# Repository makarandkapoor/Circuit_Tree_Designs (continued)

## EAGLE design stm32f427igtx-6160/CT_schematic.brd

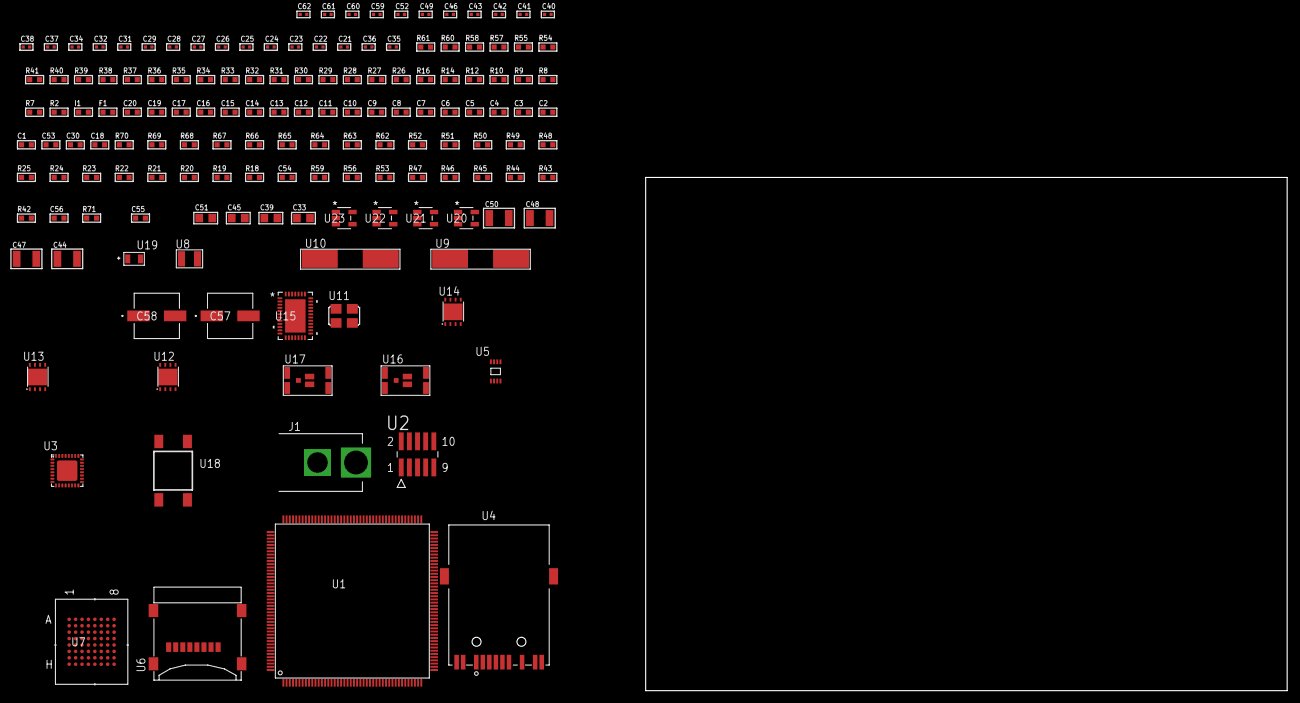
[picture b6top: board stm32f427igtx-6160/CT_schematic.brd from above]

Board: 2 copper layers, 100.0 x 80.0 mm, 150 parts (0 on the bottom side), 137 nets, no tracks yet.

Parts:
C1, C20: 1e-06; C0603
C2, C3, C4, C5, C6, C7, C8, C9, C10, C11, C12, C13, C14, C15, C16, C17: 1e-07; C0603
C18: 4.7e-06; C0603
C19: 1e-08; C0603
C21, C22, C27, C28, C29, C31, C32, C34, C38, C52: 1e-07; C0402
C23, C24, C25, C26: 1e-11; C0402
C30, C53: 2.2e-06; C0603
C33, C39, C45, C51: 1e-05; C0805
C35, C36: 2.2e-11; C0402
C37, C40, C41, C42, C43, C46, C49, C59, C60, C61, C62: 1e-08; C0402
C44, C47, C48, C50: 1e-05; C1210
C54: 2.45e-08; R0603
C55: 2.8258362168397e-09; R0603
C56: 7.105e-09; R0603
C57, C58: 0.0001; EXV-9H
F1: 240.0; L0603
I1: 97.0; R0603
J1: PJ-037B; PJ-037B_PACKAGE
R2, R36, R38, R39, R40, R55, R58, R61: 1000.0; R0603
R7, R8, R9, R32, R33, R34, R35, R37, R41: 4700.0; R0603
R10, R12, R14, R16: 2200.0; R0603
R18, R19, R20, R21, R22, R23, R24, R25, R48, R49, R50, R51, R52, R62, R64, R65, R68, R69, R70: 10000.0; R0603
R26: 5.0; R0603
R27, R28: 0.1; R0603
R29, R54, R60: 200.0; R0603
R30: 220.0; R0603
R31: 6490.0; R0603
R42, R43, R44, R45, R46, R47, R53, R56, R59: 100000.0; R0603
R57: 2231.0; R0603
R63: 75000.0; R0603
R66, R67: 95300.0; R0603
R71: 104236.36363636; R0603
U1: STM32F427IGT6; LQFP176
U2: FTSH-105-01-L-DV-K; SAMTEC_FTSH-105-01-L-DV-K
U3: KSZ8081RNBIA-TR; QFN-32
U4: 7498011122R
U5: 24AA02T-I/MNY; TDFN-8/6MM
U6: 0472192001; MOLEX_47219-2001
U7: mt28ew256aba1HPC-0SIT; LBGA-64
U8: ABS07-32.768KHZ-7-T
U9, U10: ABLS-25.000MHZ-B2F-T
U11: ASFL1-50MHZ-NCS; ASFL1
U12, U13, U14: LP3878SDX-ADJ/NOPB; WSON-8
U15: LTC2928CUHF#PBF; QFN-38_UHF
U16, U17: IRF8306MTRPbF; IRF8306MTRPBF
U18: 4-1437565-2; SW_4-1437565-2
U19: Q65110A2395; LGM67K-G1J2-24-Z
U20, U21, U22, U23: nc7sz125m5x; NC7SZ125M5X

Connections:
CLK_CRYSTAL_U1_9: C23.1, U1.9, U8.1
CLK_CRYSTAL_U1_10: C24.1, U1.10, U8.2
CLK_CRYSTAL_U1_29: C25.1, U1.29, U9.1
CLK_CRYSTAL_U1_30: C26.1, U1.30, U9.2
CLK_CRYSTAL_U3_8: C35.1, U3.8, U10.2
CLK_CRYSTAL_U3_9: C36.1, U3.9, U10.1
CLK_U1_41: U1.41, U11.3
GND: C1.2, C2.2, C3.2, C4.2, C5.2, C6.2, C7.2, C8.2, C9.2, C10.2, C11.2, C12.2, C13.2, C14.2, C15.2, C16.2, C17.2, C18.2, C19.2, C20.2, C21.2, C22.2, C23.2, C24.2, C25.2, C26.2, C27.2, C28.2, C29.2, C30.2, C31.2, C32.2, C33.2, C34.2, C35.2, C36.2, C37.2, C38.2, C39.2, C40.2, C41.2, C42.2, C43.2, C44.2, C45.2, C46.2, C47.2, C48.2, C49.2, C50.2, C51.2, C52.2, C53.2, C54.2, C55.2, C56.2, C57.2, C58.2, C59.2, C60.2, C61.2, C62.2, J1.2, R2.2, R20.2, R25.2, R26.2, R27.2, R28.2, R31.2, R33.2, R36.2, R38.2, R39.2, R40.2, R55.2, R58.2, R61.2, R63.2, R66.2, R67.2, R68.2, R69.2, R70.2, U1.14, U1.22, U1.37, U1.61, U1.71, U1.90, U1.102, U1.113, U1.126, U1.135, U1.148, U1.158, U2.3, U2.5, U3.1, U3.EXP, U4.1, U4.10, U5.4, U5.7, U6.6, U6.G1, U6.G2, U6.G3, U6.G4, U7.E8, U7.H2, U7.H7, U11.2, U12.3, U12.PAD, U13.3, U13.PAD, U14.3, U14.PAD, U15.8, U15.9, U15.10, U15.12, U15.13, U15.24, U15.25, U15.30, U15.32, U15.39, U19.C, U20.2, U20.3, U21.1, U21.3, U22.1, U22.3, U23.1, U23.3
NET_U1_31: R9.1, U1.31, U23.4
NET_U1_33: R14.1, U1.33, U3.12
NET_U1_39: C19.1, C20.1, F1.1, U1.38, U1.39
NET_U1_42: R16.1, U1.42, U3.11
NET_U1_48: R21.1, U1.48
NET_U1_58: R20.1, U1.58
NET_U1_125: C22.1, U1.125
NET_U1_164: R10.1, U1.164, U5.6
NET_U1_165: R12.1, U1.165, U5.5
NET_U1_166: R19.1, U1.166
NET_U1_171: R18.1, U1.171
NET_U1_176: U18.3, U18.4
NET_U2_9: R26.1, U2.9
NET_U3_2: C30.1, C31.1, U3.2
NET_U3_3: C32.1, I1.1, U3.3
NET_U3_10: R31.1, U3.10
NET_U3_13: R34.1, U3.13
NET_U3_14: R35.1, U3.14
NET_U3_19: R33.1, U3.19
NET_U3_20: R39.1, U3.20
NET_U3_21: R32.1, U3.21
NET_U3_28: R37.1, U3.28
NET_U3_29: R38.1, U3.29
NET_U3_31: R40.1, U3.31
NET_U3_32: R7.1, U3.32, U21.4
NET_U4_1: U3.7, U4.1
NET_U4_2: C28.1, U4.2
NET_U4_3: U3.6, U4.3
NET_U4_4: U3.5, U4.4
NET_U4_5: C29.1, U4.5
NET_U4_6: U3.4, U4.6
NET_U4_8: R28.1, U4.8
NET_U4_9: R29.1, U4.9
NET_U4_12: R30.1, U4.12
NET_U4_13: R27.1, U4.13, U4.14
NET_U7_B4: R51.1, U7.B4
NET_U7_B5: R8.1, U7.B5, U22.4
NET_U12_1: C43.1, U12.1
NET_U12_6: R54.2, R55.1, U12.6
NET_U12_8: R53.1, U12.8
NET_U13_1: C46.1, U13.1
NET_U13_6: R57.2, R58.1, U13.6
NET_U13_8: R56.1, U13.8
NET_U14_1: C49.1, U14.1
NET_U14_6: R60.2, R61.1, U14.6
NET_U14_8: R59.1, U14.8
NET_U15_3: R69.1, U15.3
NET_U15_6: R66.1, U15.6
NET_U15_7: R67.1, U15.7
NET_U15_16: R68.1, R71.1, U15.16
NET_U15_18: R65.1, U15.18
NET_U15_19: R64.1, U15.19, U15.20
NET_U15_21: R62.1, R63.1, U15.21, U20.4, U21.2, U22.2, U23.2
NET_U15_22: C52.1, R62.2, R64.2, R65.2, U15.11, U15.22
NET_U15_26: C55.1, U15.26
NET_U15_27: C54.1, U15.27
NET_U15_28: C56.1, U15.28
NET_U15_38: R70.1, U15.38
NET_U16_3: U15.2, U16.3
NET_U17_3: U15.37, U17.3
NET_U18_1: R2.1, U18.1, U18.2
PROC_ETH_CRS_DV: U1.53, U3.18
PROC_ETH_RXD0: R41.1, U1.54, U3.16
PROC_ETH_RXD1: R36.1, U1.55, U3.15
PROC_ETH_TXD0: U1.92, U3.24
PROC_ETH_TXD1: U1.93, U3.25
PROC_ETH_TX_EN: U1.80, U3.23
PROC_FMC_A0: U1.16, U7.E2
PROC_FMC_A1: U1.17, U7.D2
PROC_FMC_A2: U1.18, U7.C2
PROC_FMC_A3: U1.19, U7.A2
PROC_FMC_A4: U1.20, U7.B2
PROC_FMC_A5: U1.21, U7.D3
PROC_FMC_A6: U1.60, U7.C3
PROC_FMC_A7: U1.63, U7.A3
PROC_FMC_A8: U1.64, U7.B6
PROC_FMC_A9: U1.65, U7.A6
PROC_FMC_A10: U1.66, U7.C6
PROC_FMC_A11: U1.67, U7.D6
PROC_FMC_A12: U1.106, U7.B7
PROC_FMC_A13: U1.107, U7.A7
PROC_FMC_A14: U1.108, U7.C7
PROC_FMC_A15: U1.109, U7.D7
PROC_FMC_A16: U1.99, U7.E7
PROC_FMC_A17: U1.100, U7.B3
PROC_FMC_A18: U1.101, U7.C4
PROC_FMC_A19: U1.2, U7.D5
PROC_FMC_A20: U1.3, U7.D4
PROC_FMC_A21: U1.4, U7.C5
PROC_FMC_A22: U1.5, U7.B8
PROC_FMC_A23: U1.1, U7.C8
PROC_FMC_D0: U1.104, U7.E3
PROC_FMC_D1: U1.105, U7.H3
PROC_FMC_D2: U1.142, U7.E4
PROC_FMC_D3: U1.143, U7.H4
PROC_FMC_D4: U1.68, U7.H5
PROC_FMC_D5: U1.69, U7.E5
PROC_FMC_D6: U1.70, U7.H6
PROC_FMC_D7: U1.73, U7.E6
PROC_FMC_D8: U1.74, U7.F3
PROC_FMC_D9: U1.75, U7.G3
PROC_FMC_D10: U1.76, U7.F4
PROC_FMC_D11: U1.77, U7.G4
PROC_FMC_D12: U1.78, U7.F5
PROC_FMC_D13: U1.96, U7.G6
PROC_FMC_D14: U1.97, U7.F6
PROC_FMC_D15: U1.98, U7.G7
PROC_FMC_NBL0: R52.1, U1.169, U7.F7
PROC_FMC_NE2: R48.1, U1.152, U7.F2
PROC_FMC_NOE: R49.1, U1.146, U7.G2
PROC_FMC_NWAIT: U1.150, U7.A4
PROC_FMC_NWE: R50.1, U1.147, U7.A5
PROC_SDIO_CK: R43.1, U1.141, U6.5
PROC_SDIO_CMD: R42.1, U1.144, U6.3
PROC_SDIO_D0: R44.1, U1.117, U6.7
PROC_SDIO_D1: R45.1, U1.118, U6.8
PROC_SDIO_D2: R46.1, U1.139, U6.1
PROC_SDIO_D3: R47.1, U1.140, U6.2
PROC_SYS_JTCK_SWCLK: R25.1, U1.137, U2.4
PROC_SYS_JTDI: R23.1, U1.138, U2.8
PROC_SYS_JTDO_SWO: U1.161, U2.6
PROC_SYS_JTMS_SWDIO: R24.1, U1.124, U2.2
RST_OUT_U2_JTAG_RST_B: R22.1, U2.10, U20.1
VCC_12V8: C53.1, C57.1, C58.1, J1.1, R71.2, U15.23, U16.1, U16.2, U16.6, U16.7, U17.1, U17.2, U17.6, U17.7
VCC_S1_12V8: C44.1, C47.1, R53.2, R56.2, U12.4, U13.4, U16.4, U16.5
VCC_S2_12V8: C50.1, R59.2, U14.4, U17.4, U17.5
VCC_TIER1_1V2: C21.1, C45.1, R54.1, U1.81, U12.5
VCC_TIER1_3V3: C1.1, C2.1, C3.1, C4.1, C5.1, C6.1, C7.1, C8.1, C9.1, C10.1, C11.1, C12.1, C13.1, C14.1, C15.1, C16.1, C17.1, C18.1, C27.1, C33.1, C34.1, C37.1, C38.1, C39.1, C40.1, C41.1, C42.1, C48.1, C59.1, C60.1, C61.1, C62.1, F1.2, I1.2, R7.2, R8.2, R9.2, R10.2, R12.2, R14.2, R16.2, R18.2, R19.2, R21.2, R22.2, R23.2, R24.2, R32.2, R34.2, R35.2, R37.2, R41.2, R42.2, R43.2, R44.2, R45.2, R46.2, R47.2, R48.2, R49.2, R50.2, R51.2, R52.2, R57.1, U1.6, U1.15, U1.23, U1.36, U1.49, U1.62, U1.72, U1.82, U1.91, U1.103, U1.114, U1.127, U1.136, U1.149, U1.159, U1.172, U2.1, U3.17, U5.8, U6.4, U7.D8, U7.F1, U7.G5, U11.4, U13.5, U20.5, U21.5, U22.5, U23.5
VCC_TIER2_1V2: C51.1, R60.1, U14.5

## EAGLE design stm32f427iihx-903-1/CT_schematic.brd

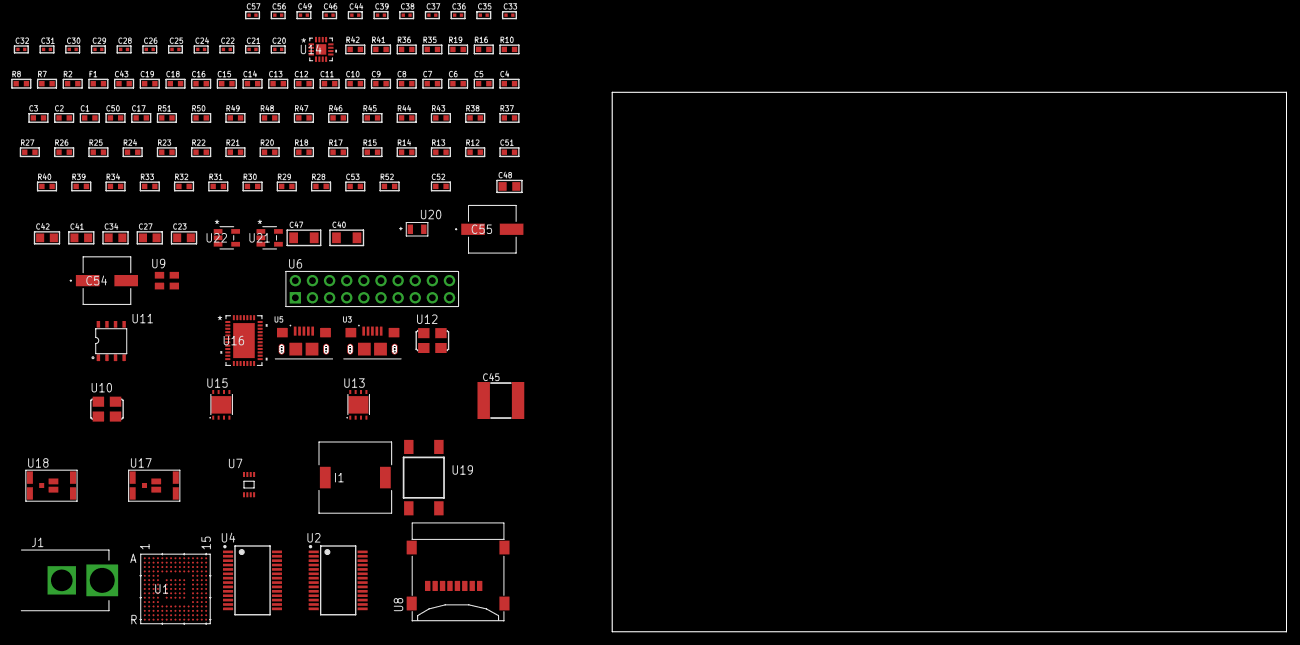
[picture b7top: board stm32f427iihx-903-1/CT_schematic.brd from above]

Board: 2 copper layers, 127 parts (0 on the bottom side), 78 nets, no tracks yet.

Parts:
C1, C19, C43: 1e-06; C0603
C2, C3, C4, C5, C6, C7, C8, C9, C10, C11, C12, C13, C14, C15, C16: 1e-07; C0603
C17: 4.7e-06; C0603
C18: 1e-08; C0603
C20, C21, C22, C24, C25, C26, C28, C29, C30, C31, C33, C44, C49: 1e-07; C0402
C23, C27: 4.7e-06; C0805
C32, C35, C36, C37, C38, C39, C46, C56, C57: 1e-08; C0402
C34, C41, C42, C48: 1e-05; C0805
C40, C47: 1e-05; C1206
C45: 6.8e-05; 2220
C50: 2.2e-06; C0603
C51: 2.45e-08; R0603
C52: 2.8258362168397e-09; R0603
C53: 7.105e-09; R0603
C54, C55: 0.0001; EXV-9H
F1: 240.0; L0603
I1: 3.8e-06; DR1040
J1: PJ-037B; PJ-037B_PACKAGE
R2, R36, R42: 1000.0; R0603
R7, R16, R19: 4700.0; R0603
R8, R10: 2200.0; R0603
R12, R13, R14, R15, R17, R18, R20, R21, R22, R23, R24, R25, R26, R27, R43, R45, R46, R49, R50, R51: 10000.0; R0603
R28, R29, R30, R31, R32, R33, R34, R40: 100000.0; R0603
R35, R41: 200.0; R0603
R37: 20000.0; R0603
R38: 91000.0; R0603
R39: 300000.0; R0603
R44: 75000.0; R0603
R47, R48: 95300.0; R0603
R52: 84636.363636364; R0603
U1: STM32F427IIH6; UFBGA176_25
U2, U4: FT232RL-REEL; SSOP-28
U3, U5: 10118193-0001LF; FCI_10118193-0001LF
U6: TST-110-05-T-D-RA
U7: 24AA01T-I/MNY; TDFN-8/6MM
U8: 0472192001; MOLEX_47219-2001
U9: ASEK-32.768KHz-ECST; ASEK
U10: ASFL1-12MHZ-NCS; ASFL1
U11: idt74fct38072; IDT74FCT38072
U12: ASFL1-25MHZ-NCS; ASFL1
U13, U15: LP3878SDX-ADJ/NOPB; WSON-8
U14: LTC3601EUD#PBF; QFN-16_EP
U16: LTC2928CUHF#PBF; QFN-38_UHF
U17, U18: IRF8306MTRPbF; IRF8306MTRPBF
U19: 4-1437565-2; SW_4-1437565-2
U20: Q65110A2395; LGM67K-G1J2-24-Z
U21, U22: nc7sz125m5x; NC7SZ125M5X

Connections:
CLK_U1_E1: U1.E1, U9.3
CLK_U1_G1: U1.G1, U12.3
CLK_U2_27: U2.27, U11.7
CLK_U4_27: U4.27, U11.6
CLK_U11_3: U10.3, U11.3
GND: C1.2, C2.2, C3.2, C4.2, C5.2, C6.2, C7.2, C8.2, C9.2, C10.2, C11.2, C12.2, C13.2, C14.2, C15.2, C16.2, C17.2, C18.2, C19.2, C20.2, C21.2, C22.2, C23.2, C24.2, C25.2, C26.2, C27.2, C28.2, C29.2, C30.2, C31.2, C32.2, C33.2, C34.2, C35.2, C36.2, C37.2, C38.2, C39.2, C40.2, C41.2, C42.2, C43.2, C45.1, C45.2, C46.2, C47.2, C48.2, C49.2, C50.2, C51.2, C52.2, C53.2, C54.2, C55.2, C56.2, C57.2, J1.2, R2.2, R18.2, R21.2, R27.2, R36.2, R37.2, R39.2, R42.2, R44.2, R47.2, R48.2, R49.2, R50.2, R51.2, U1.D5, U1.D7, U1.D8, U1.D9, U1.F2, U1.F6, U1.F7, U1.F8, U1.F9, U1.F10, U1.F12, U1.G2, U1.G6, U1.G7, U1.G8, U1.G9, U1.G10, U1.G12, U1.H6, U1.H7, U1.H8, U1.H9, U1.H10, U1.H12, U1.J6, U1.J7, U1.J8, U1.J9, U1.J10, U1.K6, U1.K7, U1.K8, U1.K9, U1.K10, U1.M1, U1.M8, U1.M9, U1.N1, U2.7, U2.18, U2.21, U2.25, U2.26, U3.5, U3.6, U3.7, U3.8, U3.9, U4.7, U4.18, U4.21, U4.25, U4.26, U5.5, U5.6, U5.7, U5.8, U5.9, U6.4, U6.6, U6.8, U6.10, U6.12, U6.14, U6.16, U6.18, U6.20, U7.4, U8.6, U8.G1, U8.G2, U8.G3, U8.G4, U9.2, U10.2, U11.4, U11.5, U11.8, U12.2, U13.3, U13.PAD, U14.1, U14.9, U14.17, U15.3, U15.PAD, U16.8, U16.9, U16.10, U16.12, U16.13, U16.24, U16.25, U16.30, U16.32, U16.39, U20.C, U21.2, U21.3, U22.1, U22.3
NET_U1_A5: R8.1, U1.A5, U7.6
NET_U1_B4: R10.1, U1.B4, U7.5
NET_U1_C6: R12.1, U1.C6
NET_U1_D6: R13.1, U1.D6
NET_U1_F13: C21.1, U1.F13
NET_U1_J1: R7.1, U1.J1, U22.4
NET_U1_L4: R15.1, U1.L4
NET_U1_M6: R14.1, U1.M6
NET_U1_R1: C18.1, C19.1, F1.1, U1.P1, U1.R1
NET_U1_R15: U19.3, U19.4
NET_U2_14: R17.1, U2.14
NET_U2_17: C24.1, U2.17
NET_U2_19: R18.1, U2.19
NET_U3_1: R16.1, U3.1
NET_U3_2: U2.16, U3.2
NET_U3_3: U2.15, U3.3
NET_U4_14: R20.1, U4.14
NET_U4_17: C28.1, U4.17
NET_U4_19: R21.1, U4.19
NET_U5_1: R19.1, U5.1
NET_U5_2: U4.16, U5.2
NET_U5_3: U4.15, U5.3
NET_U6_19: R27.1, U6.19
NET_U13_1: C39.1, U13.1
NET_U13_6: R35.2, R36.1, U13.6
NET_U13_8: R34.1, U13.8
NET_U14_3: C44.2, I1.1, U14.3, U14.4
NET_U14_6: C44.1, U14.6
NET_U14_7: C43.1, U14.7, U14.12
NET_U14_10: R39.1, U14.10
NET_U14_11: R37.1, R38.1, U14.11
NET_U14_ATNET_3: I1.2, R38.2
NET_U15_1: C46.1, U15.1
NET_U15_6: R41.2, R42.1, U15.6
NET_U15_8: R40.1, U15.8
NET_U16_3: R50.1, U16.3
NET_U16_6: R47.1, U16.6
NET_U16_7: R48.1, U16.7
NET_U16_16: R49.1, R52.1, U16.16
NET_U16_18: R46.1, U16.18
NET_U16_19: R45.1, U16.19, U16.20
NET_U16_21: R43.1, R44.1, U16.21, U21.4, U22.2
NET_U16_22: C49.1, R43.2, R45.2, R46.2, U16.11, U16.22
NET_U16_26: C52.1, U16.26
NET_U16_27: C51.1, U16.27
NET_U16_28: C53.1, U16.28
NET_U16_38: R51.1, U16.38
NET_U17_3: U16.2, U17.3
NET_U18_3: U16.37, U18.3
NET_U19_1: R2.1, U19.1, U19.2
PROC_SDIO_CK: R29.1, U1.A12, U8.5
PROC_SDIO_CMD: R28.1, U1.D12, U8.3
PROC_SDIO_D0: R30.1, U1.G14, U8.7
PROC_SDIO_D1: R31.1, U1.F14, U8.8
PROC_SDIO_D2: R32.1, U1.B14, U8.1
PROC_SDIO_D3: R33.1, U1.B13, U8.2
PROC_SYS_JTCK_SWCLK: R25.1, U1.A14, U6.9
PROC_SYS_JTDI: R23.1, U1.A13, U6.5
PROC_SYS_JTDO_SWO: U1.A10, U6.13
PROC_SYS_JTMS_SWDIO: R24.1, U1.A15, U6.7
PROC_SYS_JTRST: R22.1, U1.A9, U6.3
PROC_UART7_RX: U1.K2, U2.1
PROC_UART7_TX: U1.K1, U2.5
PROC_UART8_RX: U1.A4, U4.1
PROC_UART8_TX: U1.A3, U4.5
RST_OUT_U6_SRESET_B: R26.1, U6.15, U21.1
VCC_10V6: C50.1, C54.1, C55.1, J1.1, R52.2, U16.23, U17.1, U17.2, U17.6, U17.7, U18.1, U18.2, U18.6, U18.7
VCC_S1_10V6: C40.1, C42.1, R34.2, U13.4, U14.15, U14.16, U17.4, U17.5
VCC_S2_10V6: C47.1, R40.2, U15.4, U18.4, U18.5
VCC_TIER1_1V2: C20.1, C41.1, R35.1, U1.M10, U13.5
VCC_TIER1_3V3: C1.1, C2.1, C3.1, C4.1, C5.1, C6.1, C7.1, C8.1, C9.1, C10.1, C11.1, C12.1, C13.1, C14.1, C15.1, C16.1, C17.1, C22.1, C23.1, C25.1, C26.1, C27.1, C29.1, C30.1, C31.1, C32.1, C33.1, C34.1, C35.1, C36.1, C37.1, C38.1, C45.2, C56.1, C57.1, F1.2, I1.2, R7.2, R8.2, R10.2, R12.2, R13.2, R14.2, R15.2, R17.2, R20.2, R22.2, R23.2, R24.2, R25.2, R26.2, R28.2, R29.2, R30.2, R31.2, R32.2, R33.2, R38.2, U1.C1, U1.C5, U1.C7, U1.C8, U1.C9, U1.F3, U1.G3, U1.G13, U1.H13, U1.J12, U1.J13, U1.K4, U1.N8, U1.N9, U1.N10, U2.4, U2.20, U4.4, U4.20, U6.1, U6.2, U7.7, U7.8, U8.4, U9.4, U10.4, U11.1, U11.2, U12.4, U14.8, U21.5, U22.5
VCC_TIER2_1V2: C48.1, R41.1, U15.5

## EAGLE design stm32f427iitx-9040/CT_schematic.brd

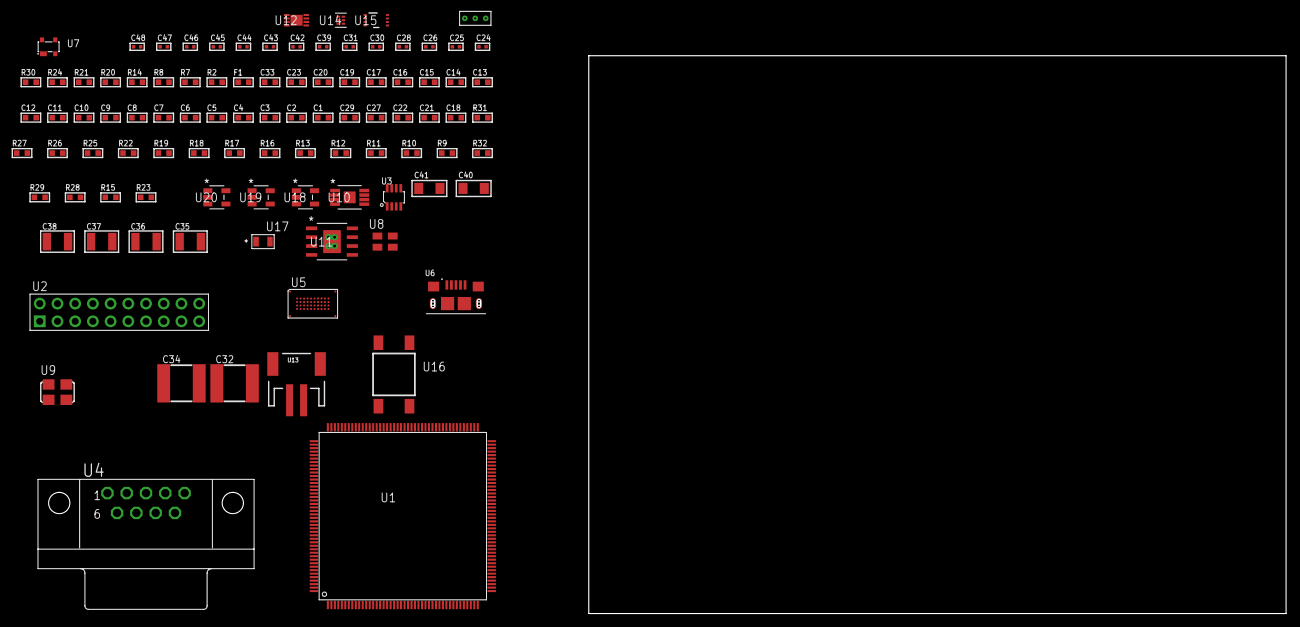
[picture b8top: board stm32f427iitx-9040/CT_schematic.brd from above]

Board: 2 copper layers, 122.6 x 80.0 mm, 97 parts (0 on the bottom side), 70 nets, no tracks yet.

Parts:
C1, C20, C23, C33: 1e-06; C0603
C2, C3, C4, C5, C6, C7, C8, C9, C10, C11, C12, C13, C14, C15, C16, C17: 1e-07; C0603
C18: 4.7e-06; C0603
C19: 1e-08; C0603
C21, C22, C27, C29: 2.2e-06; C0603
C24, C25, C26, C28, C39, C43, C45: 1e-07; C0402
C30, C31, C42, C44, C46, C47, C48: 1e-08; C0402
C32, C34: 6.8e-05; 2220
C35, C36, C37, C38: 1e-05; C1210
C40, C41: 1e-05; C1206
F1: 240.0; L0603
R2: 1000.0; R0603
R7, R8: 4700.0; R0603
R9, R10, R11, R12, R13, R16, R17, R18, R19, R22, R25, R26, R31: 10000.0; R0603
R14: 120.0; R0603
R15: 100000.0; R0603
R20: 3900.0; R0603
R21, R24: 2200.0; R0603
R23: 4031.5447154472; R0603
R27: 82000.0; R0603
R28: 300000.0; R0603
R29: 120000.0; R0603
R30: 2000.0; R0603
R32: 200000.0; R0603
U1: STM32F427IIT6; LQFP176
U2: TST-110-05-T-D-RA
U3: MAX3051EKA+T; SOT-23-8
U4: 182-009-113R531; 182-009-MALE
U5: S29VS256RABBHW000
U6: 10118193-0001LF; FCI_10118193-0001LF
U7: prtr5v0u2ax; SOT143B
U8: ASEK-32.768KHz-ECST; ASEK
U9: ASFL1-25MHZ-NCS; ASFL1
U10: MIC47100YMME; MSOP-8_EP
U11: MIC5234YME; SOIC-8_EP
U12: MCP73831T-2ACI/MC; DFN8_2X3MC
U13: S2B-PH-SM4-TB(LF)(SN); JST-2-SMD
U14: TPS3895ADRYR; SON-6
U15: LSF0102DCTR; DCU0008A_N
U16: 4-1437565-2; SW_4-1437565-2
U17: Q65110A2395; LGM67K-G1J2-24-Z
U18, U19, U20: nc7sz125m5x; NC7SZ125M5X
U21: Dummy; DUMMY_PACKAGE_209

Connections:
CLK_U1_9: U1.9, U8.3
CLK_U1_29: U1.29, U9.3
GND: C1.2, C2.2, C3.2, C4.2, C5.2, C6.2, C7.2, C8.2, C9.2, C10.2, C11.2, C12.2, C13.2, C14.2, C15.2, C16.2, C17.2, C18.2, C19.2, C20.2, C21.2, C22.2, C23.2, C24.2, C25.2, C26.2, C27.2, C28.2, C29.2, C30.2, C31.2, C32.2, C33.2, C34.2, C35.2, C36.2, C37.2, C38.2, C39.2, C40.2, C41.2, C42.2, C43.2, C44.2, C45.2, C46.2, C47.2, C48.2, R2.2, R11.2, R12.2, R15.2, R21.2, R24.2, R27.2, R29.2, R30.2, U1.14, U1.22, U1.37, U1.61, U1.71, U1.90, U1.102, U1.113, U1.122, U1.126, U1.135, U1.148, U1.158, U2.4, U2.6, U2.8, U2.10, U2.12, U2.14, U2.16, U2.18, U2.20, U3.2, U4.5, U5.C5, U5.D12, U5.E3, U5.F5, U6.5, U6.6, U6.7, U6.8, U6.9, U7.1, U8.2, U9.2, U10.3, U10.EPAD, U11.7, U11.EPAD, U12.6, U12.9, U13.2, U14.2, U15.1, U17.C, U18.2, U18.3, U19.1, U19.3, U20.1, U20.3, U21.1
INPUT_USBPOWER_5V: C23.1, C40.1, R31.2, U1.120, U6.1, U7.4, U12.1, U12.2
NET_U1_31: R8.1, U1.31, U20.4
NET_U1_39: C19.1, C20.1, F1.1, U1.38, U1.39
NET_U1_48: R12.1, U1.48
NET_U1_58: R11.1, U1.58
NET_U1_81: C21.1, U1.81
NET_U1_125: C22.1, U1.125
NET_U1_166: R10.1, U1.166
NET_U1_171: R9.1, U1.171
NET_U1_176: U16.3, U16.4
NET_U3_6: R14.2, U3.6
NET_U3_8: R15.1, U3.8
NET_U4_2: R14.2, U3.6, U4.2
NET_U4_3: R14.1, U3.7, U4.3
NET_U5_D8: R7.1, U5.D8, U19.4
NET_U10_6: R20.2, R21.1, U10.6
NET_U11_4: R23.2, R24.1, U11.4
NET_U12_5: R31.1, U12.5
NET_U12_8: R30.1, U12.8
NET_U14_1: R26.1, R27.1, U14.1
NET_U14_3: R28.2, R29.1, U14.3
NET_U14_4: R25.1, U14.4, U18.4, U19.2, U20.2
NET_U15_8: R32.1, U15.8
NET_U16_1: R2.1, U16.1, U16.2
PROC_ADC1_IN3: U1.47, U21.2
PROC_ADC1_IN4: U1.50, U21.3
PROC_CAN1_RX_TOXCVR: U3.4, U15.5
PROC_CAN1_TX_TOXCVR: U3.1, U15.6
PROC_FMC_A16: U1.99, U5.D4
PROC_FMC_A17: U1.100, U5.C11
PROC_FMC_A18: U1.101, U5.D10
PROC_FMC_A19: U1.2, U5.C10
PROC_FMC_A20: U1.3, U5.D5
PROC_FMC_A21: U1.4, U5.C4
PROC_FMC_A22: U1.5, U5.C12
PROC_FMC_A23: U1.1, U5.D7
PROC_FMC_CLK: U1.145, U5.C6
PROC_FMC_D0: U1.104, U5.F3
PROC_FMC_D1: U1.105, U5.F4
PROC_FMC_D2: U1.142, U5.E6
PROC_FMC_D3: U1.143, U5.E7
PROC_FMC_D4: U1.68, U5.F8
PROC_FMC_D5: U1.69, U5.F9
PROC_FMC_D6: U1.70, U5.E10
PROC_FMC_D7: U1.73, U5.E11
PROC_FMC_D8: U1.74, U5.E4
PROC_FMC_D9: U1.75, U5.E5
PROC_FMC_D10: U1.76, U5.F6
PROC_FMC_D11: U1.77, U5.F7
PROC_FMC_D12: U1.78, U5.E8
PROC_FMC_D13: U1.96, U5.E9
PROC_FMC_D14: U1.97, U5.F11
PROC_FMC_D15: U1.98, U5.F12
PROC_FMC_NE2: R17.1, U1.152, U5.D11
PROC_FMC_NL: U1.165, U5.D6
PROC_FMC_NOE: R19.1, U1.146, U5.E12
PROC_FMC_NWAIT: R16.1, U1.150, U5.C3
PROC_FMC_NWE: R18.1, U1.147, U5.C8
PROC_SYS_JTCK_SWCLK: U1.137, U2.9
PROC_SYS_JTDO_SWO: U1.161, U2.13
PROC_SYS_JTMS_SWDIO: U1.124, U2.7
PROC_USB_OTG_FS_DM: U1.122, U6.2, U7.3
PROC_USB_OTG_FS_DP: U1.123, U6.3, U7.2
RST_OUT_U2_SRESET_B: R13.1, U2.15, U18.1
VCC_S1_3V7: C32.1, C33.1, C35.1, C36.1, C41.1, R22.1, R22.2, U10.1, U10.2, U10.4, U10.5, U11.5, U11.8, U12.3, U12.4, U13.1
VCC_TIER1_1V8: C1.1, C2.1, C3.1, C4.1, C5.1, C6.1, C7.1, C8.1, C9.1, C10.1, C11.1, C12.1, C13.1, C14.1, C15.1, C16.1, C17.1, C18.1, C24.1, C26.1, C27.1, C28.1, C29.1, C34.1, C39.1, C44.1, C45.1, C46.1, C47.1, C48.1, F1.2, R7.2, R8.2, R9.2, R10.2, R13.2, R16.2, R17.2, R18.2, R19.2, R20.1, R25.2, R26.2, R28.1, U1.6, U1.15, U1.23, U1.36, U1.49, U1.62, U1.72, U1.82, U1.91, U1.103, U1.114, U1.127, U1.136, U1.149, U1.159, U1.172, U2.1, U5.C7, U5.D3, U5.F10, U10.7, U10.8, U14.6, U15.2, U18.5, U19.5, U20.5
VCC_TIER1_3V3: C25.1, C30.1, C31.1, C37.1, C38.1, C42.1, C43.1, R23.1, R32.2, U3.3, U8.4, U9.4, U11.1, U15.7
